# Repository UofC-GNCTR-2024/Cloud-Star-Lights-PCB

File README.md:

# Cloud-Star-Lights-PCB
Lights for the 2024 tech ex display

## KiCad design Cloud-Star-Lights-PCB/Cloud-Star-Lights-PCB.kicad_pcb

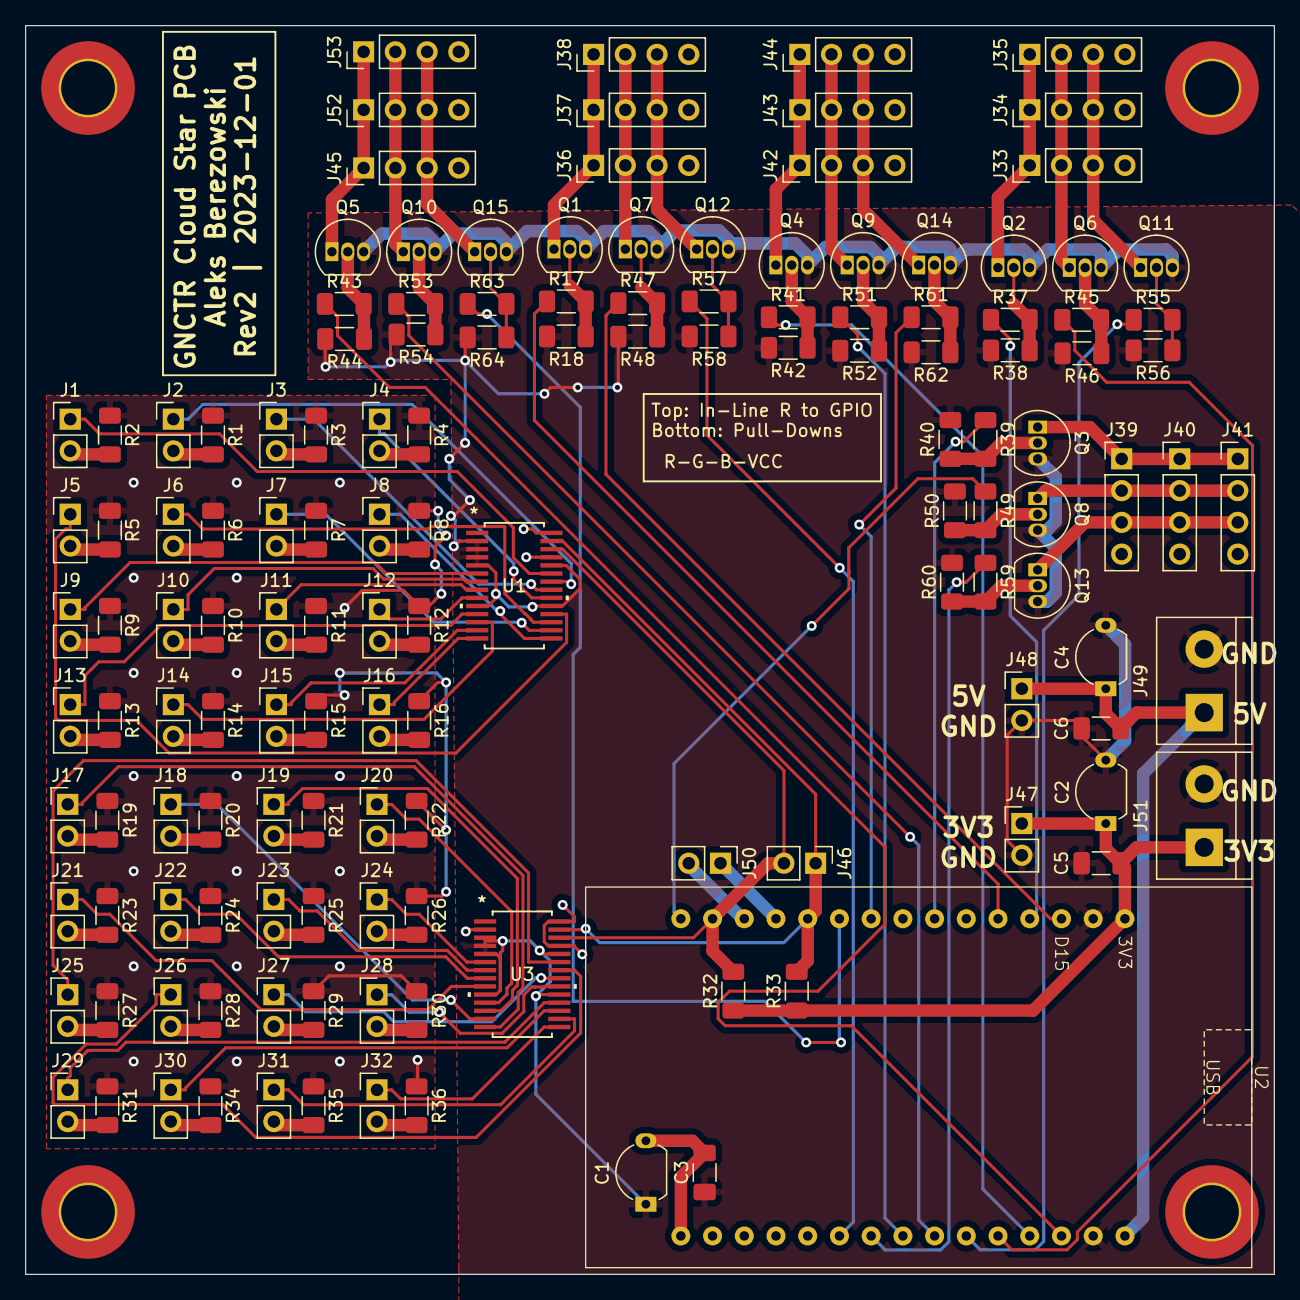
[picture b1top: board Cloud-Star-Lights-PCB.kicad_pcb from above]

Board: 2 copper layers, 100.0 x 100.0 mm, 145 parts (0 on the bottom side), 117 nets.

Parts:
C1, C2, C4: 0.1uF; SOD-70_P5.08mm
C3, C5, C6: 0.1uF; C_1206_3216Metric_Pad1.33x1.80mm_HandSolder
H1, H2, H3, H4: MountingHole_Pad; MountingHole_4.3mm_M4_DIN965_Pad_TopBottom
J1, J2, J3, J4, J5, J6, J7, J8, J9, J10, J11, J12, J13, J14, J15, J16, J17, J18, J19, J20, J21, J22, J23, J24, J25, J26, J27, J28, J29, J30, J31, J32: Conn_02x01; PinHeader_1x02_P2.54mm_Vertical
J33, J34, J35, J36, J37, J38, J39, J40, J41, J42, J43, J44, J45, J52, J53: Conn_01x04; PinHeader_1x04_P2.54mm_Vertical
J46, J47, J48, J50: Conn_01x02; PinHeader_1x02_P2.54mm_Vertical
J49, J51: Screw_Terminal_01x02; TerminalBlock_bornier-2_P5.08mm
Q1, Q2, Q3, Q4, Q5, Q6, Q7, Q8, Q9, Q10, Q11, Q12, Q13, Q14, Q15: BS170; TO-92_Inline
R1, R2, R3, R4, R5, R6, R7, R8, R9, R10, R11, R12, R13, R14, R15, R16, R19, R20, R21, R22, R23, R24, R25, R26, R27, R28, R29, R30, R31, R34, R35, R36: ?kΩ; R_1206_3216Metric_Pad1.30x1.75mm_HandSolder
R17, R37, R39, R41, R43, R45, R47, R49, R51, R53, R55, R57, R59, R61, R63: 1kΩ; R_1206_3216Metric_Pad1.30x1.75mm_HandSolder
R18, R32, R33, R38, R40, R42, R44, R46, R48, R50, R52, R54, R56, R58, R60, R62, R64: 3.3kΩ; R_1206_3216Metric_Pad1.30x1.75mm_HandSolder
U1, U3: TLC59116FIPWR
U2: ESP32-Module-30Pin

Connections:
+3.3V: C2.1, C5.2, J47.1, J51.1, R32.1, R33.1, U2.1 (3V3)
+5V: C4.1, C6.2, J33.4, J34.4, J35.4, J36.4, J37.4, J38.4, J39.4, J40.4, J41.4, J42.4, J43.4, J44.4, J45.4, J48.1, J49.1, J52.4, J53.4, R1.1, R2.1, R3.1, R4.1, R5.1, R6.1, R7.1, R8.1, R9.1, R10.1, R11.1, R12.1, R13.1, R14.1, R15.1, R16.1, R19.1, R20.1, R21.1, R22.1, R23.1, R24.1, R25.1, R26.1, R27.1, R28.1, R29.1, R30.1, R31.1, R34.1, R35.1, R36.1, U1.25 (*RESET), U1.28 (VCC), U2.30 (VIN), U3.2 (A0), U3.25 (*RESET), U3.28 (VCC)
/CloudController/Output1: J33.1, J34.1, J35.1, Q2.1 (D)
/CloudController/Output2: J36.1, J37.1, J38.1, Q1.1 (D)
/CloudController/Output3: J39.1, J40.1, J41.1, Q3.1 (D)
/CloudController/Output4: J42.1, J43.1, J44.1, Q4.1 (D)
/CloudController/Output5: J45.1, J52.1, J53.1, Q5.1 (D)
/CloudController/Output6: J33.2, J34.2, J35.2, Q6.1 (D)
/CloudController/Output7: J36.2, J37.2, J38.2, Q7.1 (D)
/CloudController/Output8: J39.2, J40.2, J41.2, Q8.1 (D)
/CloudController/Output9: J42.2, J43.2, J44.2, Q9.1 (D)
/CloudController/Output10: J45.2, J52.2, J53.2, Q10.1 (D)
/CloudController/Output11: J33.3, J34.3, J35.3, Q11.1 (D)
/CloudController/Output12: J36.3, J37.3, J38.3, Q12.1 (D)
/CloudController/Output13: J39.3, J40.3, J41.3, Q13.1 (D)
/CloudController/Output14: J42.3, J43.3, J44.3, Q14.1 (D)
/CloudController/Output15: J45.3, J52.3, J53.3, Q15.1 (D)
/Control1: R37.1, U2.4 (D2/ADC2_CH2/TOUCH2)
/Control2: R17.1, U2.5 (D4/ADC2_CH0/TOUCH0)
/Control3: R39.1, U2.7 (TX2/D17)
/Control4: R41.1, U2.27 (D12/ADC2_CH5/TOUCH5/HSPI_MISO)
/Control5: R43.1, U2.28 (D13/ADC2_CH4/TOUCH4/HSPI_MOSI)
/Control6: R45.1, U2.26 (D14/ADC2_CH6/TOUCH6/HSPI_CLK)
/Control7: R47.1, U2.3 (D15/ADC2_CH3/TOUCH3/HSPI_CS0)
/Control8: R49.1, U2.15 (D23/VSPI_MOSI)
/Control9: R51.1, U2.23 (D25/ADC2_CH8/DAC1)
/Control10: R53.1, U2.24 (D26/ADC2_CH9/DAC2)
/Control11: R55.1, U2.25 (D27/ADC2_CH7/TOUCH7)
/Control12: R57.1, U2.21 (D32/ADC1_CH4/TOUCH9)
/Control13: R59.1, U2.22 (D33/ADC1_CH5/TOUCH8)
/Control14: R61.1, U2.9 (D18/VSPI_CLK)
/Control15: R63.1, U2.10 (D19/VSPI_MISO)
/SCL: J46.2, R32.2, U1.26 (SCL), U2.14 (D22/I2C_SCL), U3.26 (SCL)
/SDA: J46.1, R33.2, U1.27 (SDA), U2.11 (D21/I2C_SDA), U3.27 (SDA)
GND: C1.1, C2.2, C3.1, C4.2, C5.1, C6.1, J47.2, J48.2, J49.2, J51.2, Q1.3 (S), Q2.3 (S), Q3.3 (S), Q4.3 (S), Q5.3 (S), Q6.3 (S), Q7.3 (S), Q8.3 (S), Q9.3 (S), Q10.3 (S), Q11.3 (S), Q12.3 (S), Q13.3 (S), Q14.3 (S), Q15.3 (S), R18.2, R38.2, R40.2, R42.2, R44.2, R46.2, R48.2, R50.2, R52.2, R54.2, R56.2, R58.2, R60.2, R62.2, R64.2, U1.2 (A0), U1.3 (A1), U1.4 (A2), U1.5 (A3), U1.10 (GND), U1.19 (GND), U1.24 (GND), U2.2 (GND_2), U2.29 (GND_1), U3.3 (A1), U3.4 (A2), U3.5 (A3), U3.10 (GND), U3.19 (GND), U3.24 (GND)
unnamed: J1.1, U1.23 (*OUT15)
unnamed: J1.2, R2.2
unnamed: J2.1, U1.22 (*OUT14)
unnamed: J2.2, R1.2
unnamed: J3.1, U1.21 (*OUT13)
unnamed: J3.2, R3.2
unnamed: J4.1, U1.20 (*OUT12)
unnamed: J4.2, R4.2
unnamed: J5.1, U1.18 (*OUT11)
unnamed: J5.2, R5.2
unnamed: J6.1, U1.17 (*OUT10)
unnamed: J6.2, R6.2
unnamed: J7.1, U1.16 (*OUT9)
unnamed: J7.2, R7.2
unnamed: J8.1, U1.15 (*OUT8)
unnamed: J8.2, R8.2
unnamed: J9.1, U1.6 (*OUT0)
unnamed: J9.2, R9.2
unnamed: J10.1, U1.7 (*OUT1)
unnamed: J10.2, R10.2
unnamed: J11.1, U1.8 (*OUT2)
unnamed: J11.2, R11.2
unnamed: J12.1, U1.9 (*OUT3)
unnamed: J12.2, R12.2
unnamed: J13.1, U1.11 (*OUT4)
unnamed: J13.2, R13.2
unnamed: J14.1, U1.12 (*OUT5)
unnamed: J14.2, R14.2
unnamed: J15.1, U1.13 (*OUT6)
unnamed: J15.2, R15.2
unnamed: J16.1, U1.14 (*OUT7)
unnamed: J16.2, R16.2
unnamed: J17.1, U3.14 (*OUT7)
unnamed: J17.2, R19.2
unnamed: J18.1, U3.13 (*OUT6)
unnamed: J18.2, R20.2
unnamed: J19.1, U3.12 (*OUT5)
unnamed: J19.2, R21.2
unnamed: J20.1, U3.11 (*OUT4)
unnamed: J20.2, R22.2
unnamed: J21.1, U3.9 (*OUT3)
unnamed: J21.2, R23.2
unnamed: J22.1, U3.8 (*OUT2)
unnamed: J22.2, R24.2
unnamed: J23.1, U3.7 (*OUT1)
unnamed: J23.2, R25.2
unnamed: J24.1, U3.6 (*OUT0)
unnamed: J24.2, R26.2
unnamed: J25.1, U3.23 (*OUT15)
unnamed: J25.2, R27.2
unnamed: J26.1, U3.22 (*OUT14)
unnamed: J26.2, R28.2
unnamed: J27.1, U3.21 (*OUT13)
unnamed: J27.2, R29.2
unnamed: J28.1, U3.20 (*OUT12)
unnamed: J28.2, R30.2
unnamed: J29.1, U3.18 (*OUT11)
unnamed: J29.2, R31.2
unnamed: J30.1, U3.17 (*OUT10)
unnamed: J30.2, R34.2
unnamed: J31.1, U3.16 (*OUT9)
unnamed: J31.2, R35.2
unnamed: J32.1, U3.15 (*OUT8)
unnamed: J32.2, R36.2
unnamed: J50.1, U2.12 (RX0/D3)
unnamed: J50.2, U2.13 (TX0/D1)
unnamed: Q1.2 (G), R17.2, R18.1
unnamed: Q2.2 (G), R37.2, R38.1
unnamed: Q3.2 (G), R39.2, R40.1
unnamed: Q4.2 (G), R41.2, R42.1
unnamed: Q5.2 (G), R43.2, R44.1
unnamed: Q6.2 (G), R45.2, R46.1
unnamed: Q7.2 (G), R47.2, R48.1
unnamed: Q8.2 (G), R49.2, R50.1
unnamed: Q9.2 (G), R51.2, R52.1
unnamed: Q10.2 (G), R53.2, R54.1
unnamed: Q11.2 (G), R55.2, R56.1
unnamed: Q12.2 (G), R57.2, R58.1
unnamed: Q13.2 (G), R59.2, R60.1
unnamed: Q14.2 (G), R61.2, R62.1
unnamed: Q15.2 (G), R63.2, R64.1
unnamed: C1.2, C3.2, U2.16 (EN)

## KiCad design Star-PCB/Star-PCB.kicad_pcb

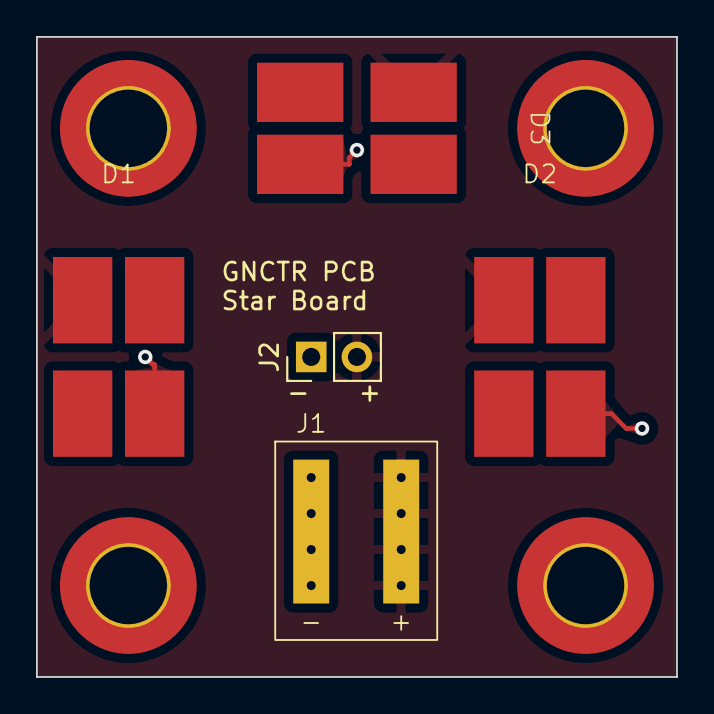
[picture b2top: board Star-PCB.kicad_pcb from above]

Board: 2 copper layers, 35.6 x 35.6 mm, 9 parts (0 on the bottom side), 2 nets.

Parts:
D1, D2, D3: LY_E65F-DAEA-35-3B5A-50-R33-Z
H1, H2, H3, H4: MountingHole_Pad; MountingHole_4.3mm_M4_ISO7380_Pad_TopBottom
J1: Conn_01x02; star_connector
J2: Conn_01x02; PinHeader_1x02_P2.54mm_Vertical

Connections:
unnamed: D1.2, D2.2, D3.2, J1.1, J2.1
unnamed: D1.1, D2.1, D3.1, J1.2, J2.2

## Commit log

2023-10-10 Draft1
2023-10-11 Convert to ESP chip and localize library (hopefully)
2023-10-13 Praying to god my library is right
2023-10-18 Make star schematic
2023-10-19 Hopefully make PCB?
2023-10-19 Fixed it
2023-10-21 Schematics Done
2023-10-23 Comments
2023-10-23 Fix .gitignore rules
2023-10-23 Schematic changes
2023-10-25 Schematic
2023-10-27 Move files up a level
2023-10-27 Fix Footprint Libraries
    * Removed the bad row with an absolute path in the Symbol Editor > Manage Symbol Lib paths
    * Updated the ESP32 symbol to pull from the right lib
    *
2023-10-27 Change a connector to a screw terminal
2023-10-27 Change paper to A2
2023-10-27 Assign footprint to screw terminal
2023-10-28 before I run the autoroute4
2023-10-28 main2: ERC Check
2023-10-28 main2: Manual routing
2023-10-28 main2: All done :)
2023-10-28 DONE!
2023-10-28 DONE! (v2)
2023-10-28 DONE! (v3)
2023-11-29 Schematic v2
2023-11-29 Update I2C addresses
2023-11-30 Starting routing
2023-11-30 Unrouted board
2023-11-30 Routing done!
2023-12-01 Routing
2023-12-01 Finalize rev2 order
    - added comments, silk screens
    - exported PDF and gerber
